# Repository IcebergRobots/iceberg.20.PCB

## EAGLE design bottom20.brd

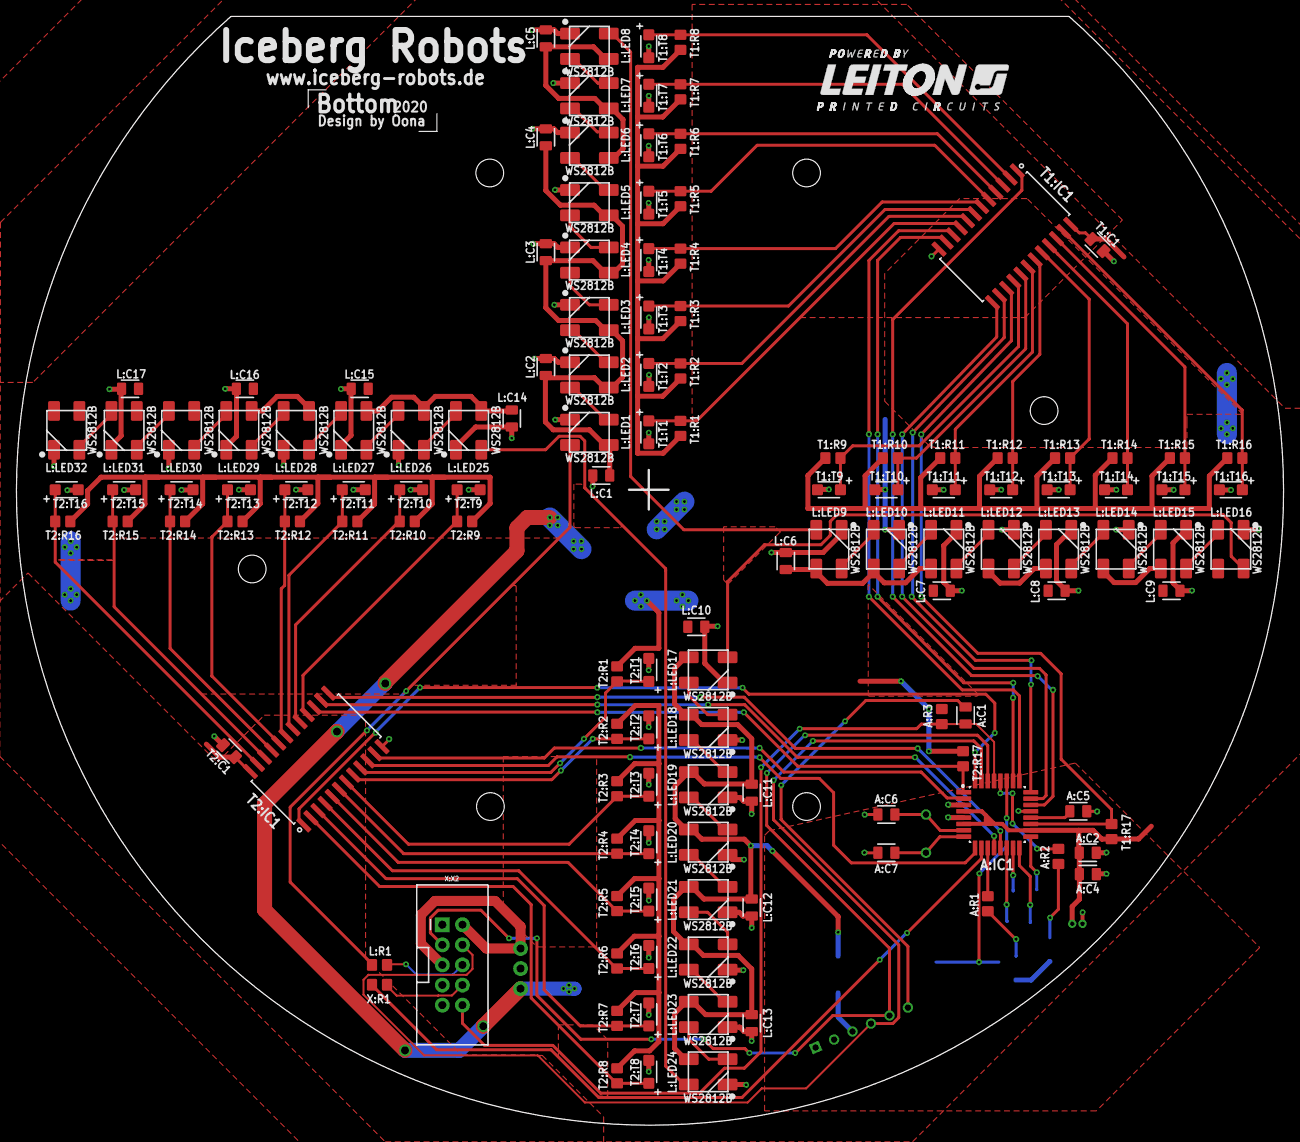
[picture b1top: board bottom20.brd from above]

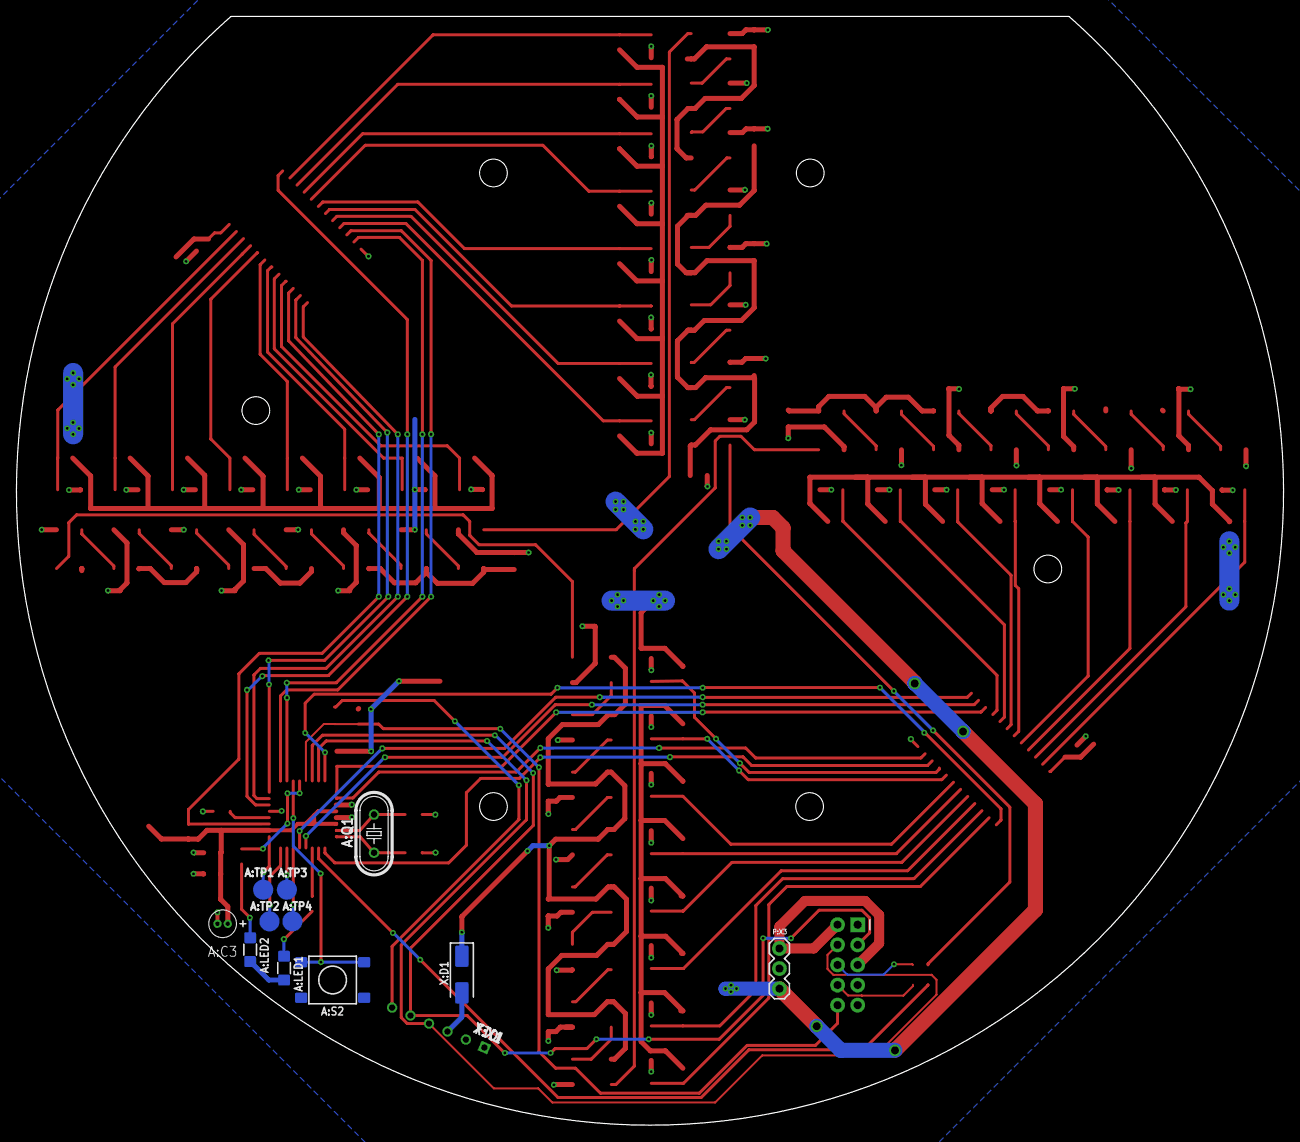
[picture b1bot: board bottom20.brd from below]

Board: 2 copper layers, 160.0 x 140.0 mm, 144 parts (12 on the bottom side), 99 nets.

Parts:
A:C1, A:C5: 100n; C0805
A:C2, A:C4: 1u; C0805
A:C3: 4,7 µF, 16 V, ±20%, 3x5 mm; CAPACITOR-THT-3
A:C6, A:C7: 15p; C0805
A:IC1: ATMEGA328P-AU
A:LED1, A:LED2: LED-GREEN1; 1206
A:Q1: 16MHz; CRYSTAL_HC49U-V
A:R1, A:R2: 110R; R0805
A:R3: 100k; R0805
A:S2: SMD-BUTTON; SWITCH-6MM-SMD
A:TP1: SCK; TESTPAD_B2,54
A:TP2: MISO; TESTPAD_B2,54
A:TP3: MOSI; TESTPAD_B2,54
A:TP4: SS; TESTPAD_B2,54
L:C1: 1u; C0805
L:C2, L:C3, L:C4, L:C5, L:C6, L:C7, L:C8, L:C9, L:C10, L:C11, L:C12, L:C13, L:C14, L:C15, L:C16, L:C17: 100n; C0805
L:LED1, L:LED2, L:LED3, L:LED4, L:LED5, L:LED6, L:LED7, L:LED8, L:LED9, L:LED10, L:LED11, L:LED12, L:LED13, L:LED14, L:LED15, L:LED16, L:LED17, L:LED18, L:LED19, L:LED20, L:LED21, L:LED22, L:LED23, L:LED24, L:LED25, L:LED26, L:LED27, L:LED28, L:LED29, L:LED30, L:LED31, L:LED32: WS2812B; 5050
L:R1: 330R; R0805
P:X3: SCHALTREGLER; 3X1
T1:C1, T2:C1: 100nF; C0805
T1:IC1, T2:IC1: MULTIPLEXER; SO24
T1:R1, T1:R2, T1:R3, T1:R4, T1:R5, T1:R6, T1:R7, T1:R8, T1:R9, T1:R10, T1:R11, T1:R12, T1:R13, T1:R14, T1:R15, T1:R16, T2:R1, T2:R2, T2:R3, T2:R4, T2:R5, T2:R6, T2:R7, T2:R8, T2:R9, T2:R10, T2:R11, T2:R12, T2:R13, T2:R14, T2:R15, T2:R16: 20k; R0805
T1:R17, T2:R17: 10k; R0805
T1:T1, T1:T2, T1:T3, T1:T4, T1:T5, T1:T6, T1:T7, T1:T8, T1:T9, T1:T10, T1:T11, T1:T12, T1:T13, T1:T14, T1:T15, T1:T16, T2:T1, T2:T2, T2:T3, T2:T4, T2:T5, T2:T6, T2:T7, T2:T8, T2:T9, T2:T10, T2:T11, T2:T12, T2:T13, T2:T14, T2:T15, T2:T16: SFH320; PLCC-2
X:D1: DIODE; DO-214BA
X:R1: 330R; R0805
X:X1: FTDI; PIN-HEADER-ANGLED-6
X:X2: WANNENSTECKER-10; 2X5-SHROUDED

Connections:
+5V: A:C2.1, A:C3.1, A:C4.1, A:IC1.4, A:IC1.6, A:IC1.18, A:R3.2, L:C1.1, L:C2.1, L:C3.1, L:C4.1, L:C5.1, L:C6.1, L:C7.1, L:C8.1, L:C9.1, L:C10.1, L:C11.1, L:C12.1, L:C13.1, L:C14.1, L:C15.1, L:C16.1, L:C17.1, L:LED1.VDD, L:LED2.VDD, L:LED3.VDD, L:LED4.VDD, L:LED5.VDD, L:LED6.VDD, L:LED7.VDD, L:LED8.VDD, L:LED9.VDD, L:LED10.VDD, L:LED11.VDD, L:LED12.VDD, L:LED13.VDD, L:LED14.VDD, L:LED15.VDD, L:LED16.VDD, L:LED17.VDD, L:LED18.VDD, L:LED19.VDD, L:LED20.VDD, L:LED21.VDD, L:LED22.VDD, L:LED23.VDD, L:LED24.VDD, L:LED25.VDD, L:LED26.VDD, L:LED27.VDD, L:LED28.VDD, L:LED29.VDD, L:LED30.VDD, L:LED31.VDD, L:LED32.VDD, P:X3.1, T1:C1.1, T1:IC1.24, T1:R1.2, T1:R2.2, T1:R3.2, T1:R4.2, T1:R5.2, T1:R6.2, T1:R7.2, T1:R8.2, T1:R9.2, T1:R10.2, T1:R11.2, T1:R12.2, T1:R13.2, T1:R14.2, T1:R15.2, T1:R16.2, T1:R17.1, T2:C1.1, T2:IC1.24, T2:R1.2, T2:R2.2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
+12V: P:X3.3, X:X2.2, X:X2.5
A:MISO: A:IC1.16, A:TP2.TP
A:MOSI: A:IC1.15, A:TP3.TP
A:N$1: A:IC1.11, A:R1.1
A:N$2: A:C7.1, A:IC1.8, A:Q1.1
A:N$3: A:C6.2, A:IC1.7, A:Q1.2
A:N$4: A:LED1.A, A:R1.2
A:N$8: A:C5.1, A:IC1.20
A:N$9: A:IC1.27, A:S2.A1, A:S2.A2
A:N$10: A:LED2.A, A:R2.2
A:N$11: A:IC1.28, A:R2.1
A:SCK: A:IC1.17, A:TP1.TP
A:SS: A:IC1.14, A:TP4.TP
ARD-INTERRUPT: A:IC1.10, X:R1.2
ARD-RESET: A:C1.2, A:IC1.29, A:R3.1, X:X2.10
DTR: A:C1.1, X:X1.6
GND: A:C2.2, A:C3.2, A:C4.2, A:C5.2, A:C6.1, A:C7.2, A:IC1.3, A:IC1.5, A:IC1.21, A:LED1.C, A:LED2.C, A:S2.B1, A:S2.B2, L:C1.2, L:C2.2, L:C3.2, L:C4.2, L:C5.2, L:C6.2, L:C7.2, L:C8.2, L:C9.2, L:C10.2, L:C11.2, L:C12.2, L:C13.2, L:C14.2, L:C15.2, L:C16.2, L:C17.2, L:LED1.GND, L:LED2.GND, L:LED3.GND, L:LED4.GND, L:LED5.GND, L:LED6.GND, L:LED7.GND, L:LED8.GND, L:LED9.GND, L:LED10.GND, L:LED11.GND, L:LED12.GND, L:LED13.GND, L:LED14.GND, L:LED15.GND, L:LED16.GND, L:LED17.GND, L:LED18.GND, L:LED19.GND, L:LED20.GND, L:LED21.GND, L:LED22.GND, L:LED23.GND, L:LED24.GND, L:LED25.GND, L:LED26.GND, L:LED27.GND, L:LED28.GND, L:LED29.GND, L:LED30.GND, L:LED31.GND, L:LED32.GND, P:X3.2, T1:C1.2, T1:IC1.12, T1:T1.C, T1:T2.C, T1:T3.C, T1:T4.C, T1:T5.C, T1:T6.C, T1:T7.C, T1:T8.C, T1:T9.C, T1:T10.C, T1:T11.C, T1:T12.C, T1:T13.C, T1:T14.C, T1:T15.C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
L:CON-1: L:LED8.OUT, L:LED9.IN
L:CON-2: L:LED16.OUT, L:LED17.IN
L:CON-3: L:LED24.OUT, L:LED25.IN
L:LED-IN1: L:LED2.OUT, L:LED3.IN
L:LED-IN2: L:LED4.OUT, L:LED5.IN
L:LED-IN3: L:LED6.OUT, L:LED7.IN
L:LED-IN4: L:LED26.OUT, L:LED27.IN
L:LED-IN5: L:LED10.OUT, L:LED11.IN
L:LED-IN6: L:LED12.OUT, L:LED13.IN
L:LED-IN7: L:LED14.OUT, L:LED15.IN
L:LED-IN8: L:LED28.OUT, L:LED29.IN
L:LED-IN9: L:LED18.OUT, L:LED19.IN
L:LED-IN10: L:LED20.OUT, L:LED21.IN
L:LED-IN11: L:LED22.OUT, L:LED23.IN
L:LED-IN12: L:LED30.OUT, L:LED31.IN
L:N$1: L:LED3.OUT, L:LED4.IN
L:N$2: L:LED1.OUT, L:LED2.IN
L:N$3: L:LED25.OUT, L:LED26.IN
L:N$4: L:LED5.OUT, L:LED6.IN
L:N$5: L:LED27.OUT, L:LED28.IN
L:N$6: L:LED29.OUT, L:LED30.IN
L:N$7: L:LED7.OUT, L:LED8.IN
L:N$8: L:LED31.OUT, L:LED32.IN
L:N$9: L:LED9.OUT, L:LED10.IN
L:N$10: L:LED1.IN, L:R1.1
L:N$11: L:LED11.OUT, L:LED12.IN
L:N$12: L:LED13.OUT, L:LED14.IN
L:N$13: L:LED15.OUT, L:LED16.IN
L:N$14: L:LED17.OUT, L:LED18.IN
L:N$16: L:LED19.OUT, L:LED20.IN
L:N$17: L:LED21.OUT, L:LED22.IN
L:N$18: L:LED23.OUT, L:LED24.IN
LED-IN: L:R1.2, X:X2.6
unnamed: A:IC1.32, T2:IC1.1
unnamed: A:IC1.1, T2:IC1.15, T2:R17.2
unnamed: A:IC1.2, T2:IC1.11
unnamed: A:IC1.9, T2:IC1.10
unnamed: A:IC1.12, T2:IC1.14
unnamed: A:IC1.13, T2:IC1.13
unnamed: A:IC1.23, T1:IC1.13
unnamed: A:IC1.24, T1:IC1.14
unnamed: A:IC1.25, T1:IC1.10
unnamed: A:IC1.26, T1:IC1.11
unnamed: A:IC1.19, T1:IC1.15, T1:R17.2
unnamed: A:IC1.22, T1:IC1.1
RX: A:IC1.30, X:X1.5, X:X2.3
T1:N$1: T1:IC1.9, T1:R1.1, T1:T1.A
T1:N$2: T1:IC1.8, T1:R2.1, T1:T2.A
T1:N$3: T1:IC1.7, T1:R3.1, T1:T3.A
T1:N$4: T1:IC1.6, T1:R4.1, T1:T4.A
T1:N$5: T1:IC1.5, T1:R5.1, T1:T5.A
T1:N$7: T1:IC1.16, T1:R9.1, T1:T9.A
T1:N$9: T1:IC1.2, T1:R8.1, T1:T8.A
T1:N$10: T1:IC1.3, T1:R7.1, T1:T7.A
T1:N$11: T1:IC1.4, T1:R6.1, T1:T6.A
T1:N$12: T1:IC1.17, T1:R10.1, T1:T10.A
T1:N$14: T1:IC1.18, T1:R11.1, T1:T11.A
T1:N$18: T1:IC1.20, T1:R13.1, T1:T13.A
T1:N$20: T1:IC1.21, T1:R14.1, T1:T14.A
T1:N$22: T1:IC1.22, T1:R15.1, T1:T15.A
T1:N$25: T1:IC1.23, T1:R16.1, T1:T16.A
T1:N$26: T1:IC1.19, T1:R12.1, T1:T12.A
T2:N$1: T2:IC1.9, T2:R1.1, T2:T1.A
T2:N$2: T2:IC1.8, T2:R2.1, T2:T2.A
T2:N$3: T2:IC1.7, T2:R3.1, T2:T3.A
T2:N$4: T2:IC1.6, T2:R4.1, T2:T4.A
T2:N$5: T2:IC1.5, T2:R5.1, T2:T5.A
T2:N$7: T2:IC1.16, T2:R9.1, T2:T9.A
T2:N$9: T2:IC1.2, T2:R8.1, T2:T8.A
T2:N$10: T2:IC1.3, T2:R7.1, T2:T7.A
T2:N$11: T2:IC1.4, T2:R6.1, T2:T6.A
T2:N$12: T2:IC1.17, T2:R10.1, T2:T10.A
T2:N$14: T2:IC1.18, T2:R11.1, T2:T11.A
T2:N$18: T2:IC1.20, T2:R13.1, T2:T13.A
T2:N$20: T2:IC1.21, T2:R14.1, T2:T14.A
T2:N$22: T2:IC1.22, T2:R15.1, T2:T15.A
T2:N$25: T2:IC1.23, T2:R16.1, T2:T16.A
T2:N$26: T2:IC1.19, T2:R12.1, T2:T12.A
TX: A:IC1.31, X:X1.4, X:X2.4
X:N$1: X:R1.1, X:X2.8
X:VID: X:D1.2, X:X1.3

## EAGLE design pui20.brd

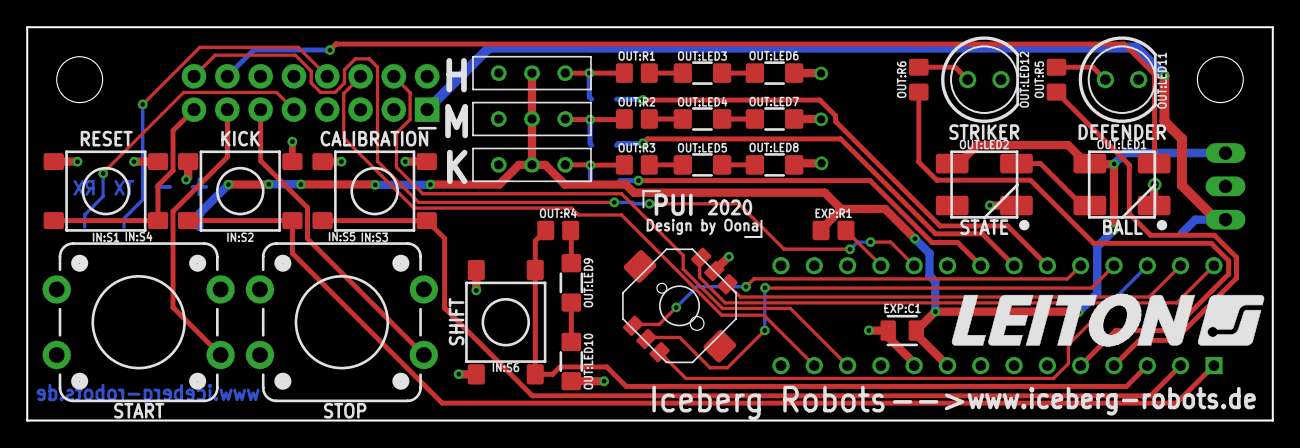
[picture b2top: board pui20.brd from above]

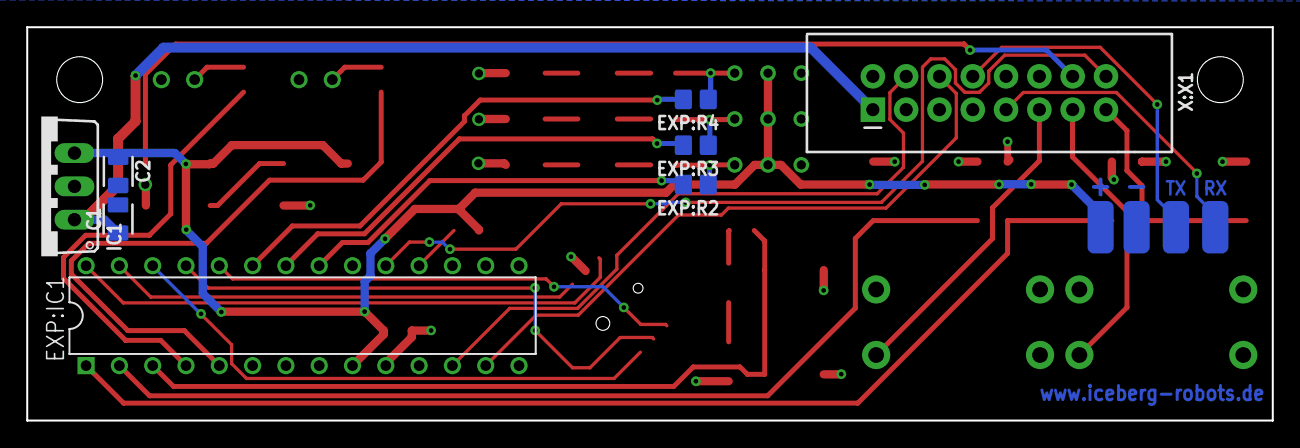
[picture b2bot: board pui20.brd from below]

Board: 2 copper layers, 95.0 x 30.0 mm, 42 parts (12 on the bottom side), 40 nets.

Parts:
C1, C2: 200nF; C0805
DISPLAY1:GND, DISPLAY1:RX, DISPLAY1:TX, DISPLAY1:VIN: TESTPAD-LONG
EXP:C1: 200nF; C0805
EXP:IC1: GPIO-EXPANDER; DIL28-3
EXP:R1: 1k; R0805
EXP:R2, EXP:R3, EXP:R4: 330R; R0805
IC1: L7805; TO220V
IN:S1, IN:S2, IN:S3, IN:S6: SMD-BUTTON; SWITCH-6MM-SMD
IN:S4, IN:S5: BUTTON-12MM; SWITCH-12MM-THT
IN:S7, IN:S8, IN:S9: TOGGLE-SWITCH
IN:U$1: JOYSTICK; SKRHAAE010
OUT:LED1, OUT:LED2: WS2812B; 5050
OUT:LED3, OUT:LED4, OUT:LED5, OUT:LED6, OUT:LED7, OUT:LED8, OUT:LED9, OUT:LED10: LED-GREEN1; 1206
OUT:LED11, OUT:LED12: LED-GREEN-THT; LED_LED5MM
OUT:R1, OUT:R2, OUT:R3, OUT:R4: 50R; R0805
OUT:R5, OUT:R6: 220R; R0805
X:X1: WANNENSTECKER-16; 2X8

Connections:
+5V: C2.1, DISPLAY1:VIN.P$1, EXP:C1.1, EXP:IC1.9, EXP:R1.2, IC1.3, IN:S7.C, IN:S8.C, IN:S9.C, OUT:LED1.VDD, OUT:LED2.VDD
+12V: C1.1, IC1.1, X:X1.1
CALIBRATION-B: EXP:IC1.2, IN:S3.A1, IN:S3.A2
CENTER-J: EXP:IC1.25, IN:U$1.CENTER
DEFENCE-LED: EXP:IC1.5, OUT:R6.1
DOWN-J: EXP:IC1.26, IN:U$1.C
EXP:N$1: EXP:IC1.21, EXP:R2.2
EXP:N$2: EXP:IC1.22, EXP:R3.2
EXP:N$3: EXP:IC1.23, EXP:R4.2
EXP:RESET: EXP:IC1.18, EXP:R1.1
GND: C1.2, C2.2, DISPLAY1:GND.P$1, EXP:C1.2, EXP:IC1.10, EXP:IC1.15, EXP:IC1.16, EXP:IC1.17, IC1.2, IN:S1.B1, IN:S1.B2, IN:S2.B1, IN:S2.B2, IN:S3.B1, IN:S3.B2, IN:S4.3, IN:S5.3, IN:S6.B1, IN:S6.B2, IN:U$1.COMMON, OUT:LED1.GND, OUT:LED2.GND, OUT:LED6.C, OUT:LED7.C, OUT:LED8.C, OUT:LED10.C, OUT:LED11.K, OUT:LED12.K, X:X1.3, X:X1.5, X:X1.7
HEADSTART-LED: EXP:R4.1, IN:S7.A, OUT:R1.1
INT-B: EXP:IC1.19, X:X1.16
KICK-B: EXP:IC1.1, IN:S2.A1, IN:S2.A2
KICKER-LED: EXP:R2.1, IN:S9.A, OUT:R3.1
LED-IN: OUT:LED1.IN, X:X1.14
LEFT-J: EXP:IC1.24, IN:U$1.A
MOTOR-LED: EXP:R3.1, IN:S8.A, OUT:R2.1
OUT:N$1: OUT:LED3.C, OUT:LED6.A
OUT:N$2: OUT:LED3.A, OUT:R1.2
OUT:N$3: OUT:LED4.C, OUT:LED7.A
OUT:N$4: OUT:LED5.C, OUT:LED8.A
OUT:N$5: OUT:LED1.OUT, OUT:LED2.IN
OUT:N$6: OUT:LED4.A, OUT:R2.2
OUT:N$7: OUT:LED5.A, OUT:R3.2
OUT:N$8: OUT:LED11.A, OUT:R5.2
OUT:N$9: OUT:LED12.A, OUT:R6.2
OUT:N$11: OUT:LED9.A, OUT:R4.2
OUT:N$12: OUT:LED9.C, OUT:LED10.A
RESET-B: IN:S1.A1, IN:S1.A2, X:X1.15
RIGHT-J: EXP:IC1.27, IN:U$1.D
RX: DISPLAY1:RX.P$1, X:X1.9
SCL: EXP:IC1.12, X:X1.4
SDA: EXP:IC1.13, X:X1.6
SHIFT-LED: EXP:IC1.3, IN:S6.A1, IN:S6.A2, OUT:R4.1
START-B: IN:S4.1, X:X1.13
STOP-B: IN:S5.1, X:X1.11
STRIKER-LED: EXP:IC1.4, OUT:R5.1
TX: DISPLAY1:TX.P$1, X:X1.8
UP-J: EXP:IC1.28, IN:U$1.B

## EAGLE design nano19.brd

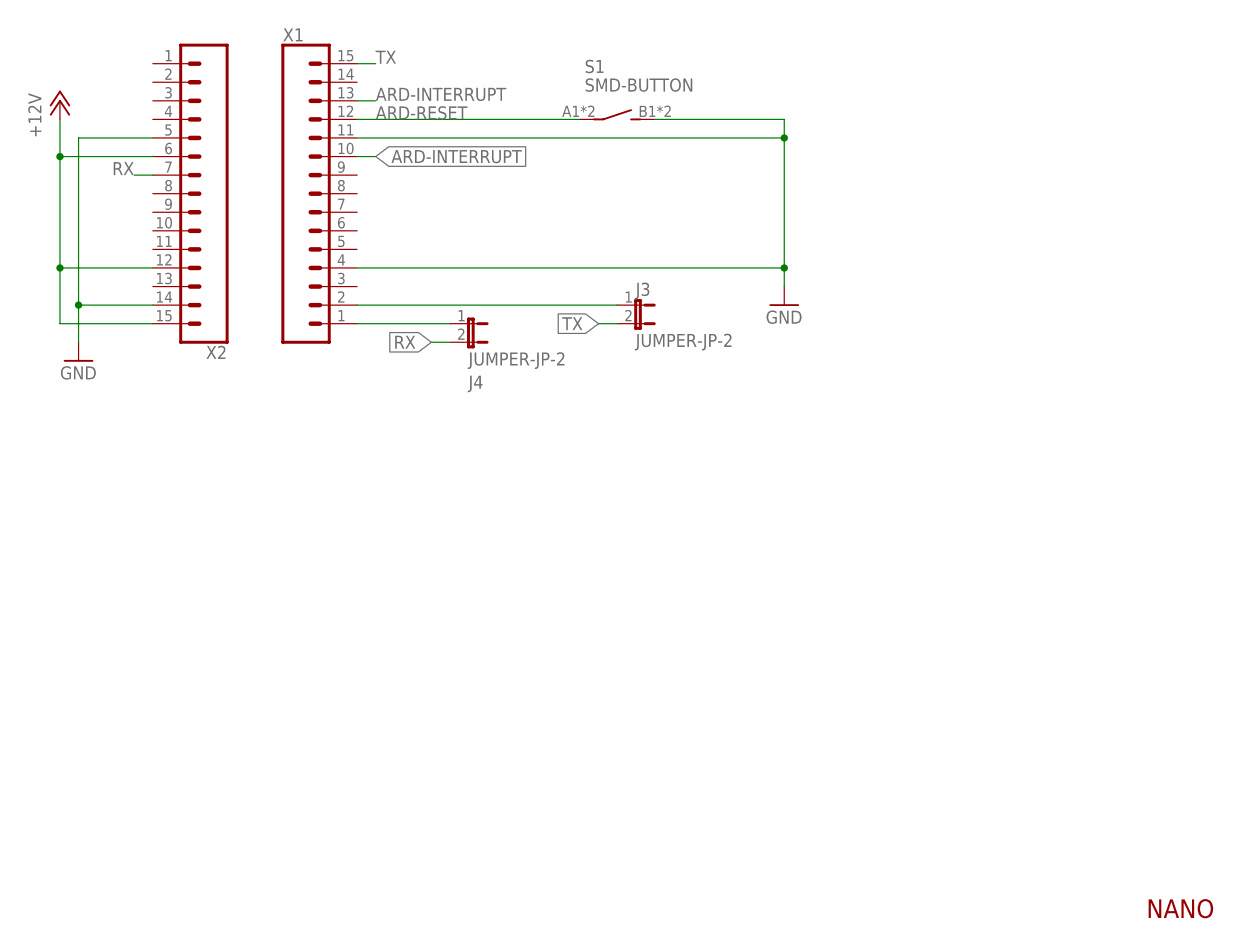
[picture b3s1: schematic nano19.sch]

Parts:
J3, J4: JUMPER-JP-2; JUMPER_JP1
S1: SMD-BUTTON; SWITCH-6MM-SMD
X1, X2: CONN_15; 1X15

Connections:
+12V: X2.6, X2.12, X2.15
ARD-INTERRUPT: X1.10, X1.13
ARD-RESET: S1.A1, S1.A2, X1.12
GND: S1.B1 (S), S1.B2 (S), X1.4, X1.11, X2.5, X2.14
unnamed: J3.1, X1.2
unnamed: J4.1, X1.1
RX: J4.2, X2.7
TX: J3.2, X1.15

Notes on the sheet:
NANO

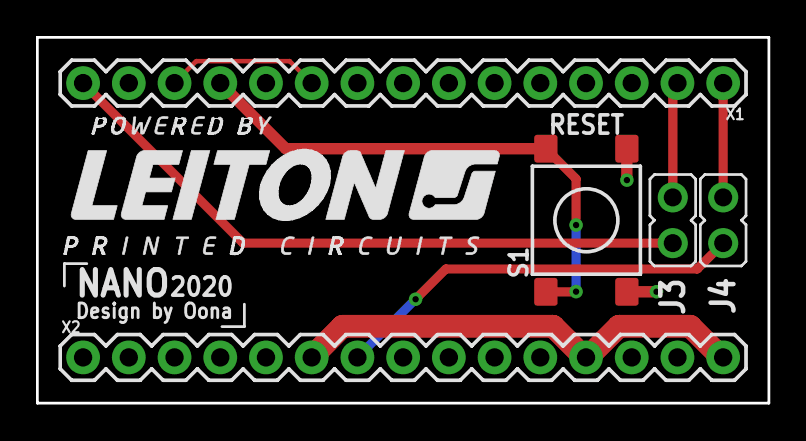
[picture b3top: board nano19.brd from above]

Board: 2 copper layers, 40.6 x 20.3 mm, 5 parts (0 on the bottom side), 8 nets.

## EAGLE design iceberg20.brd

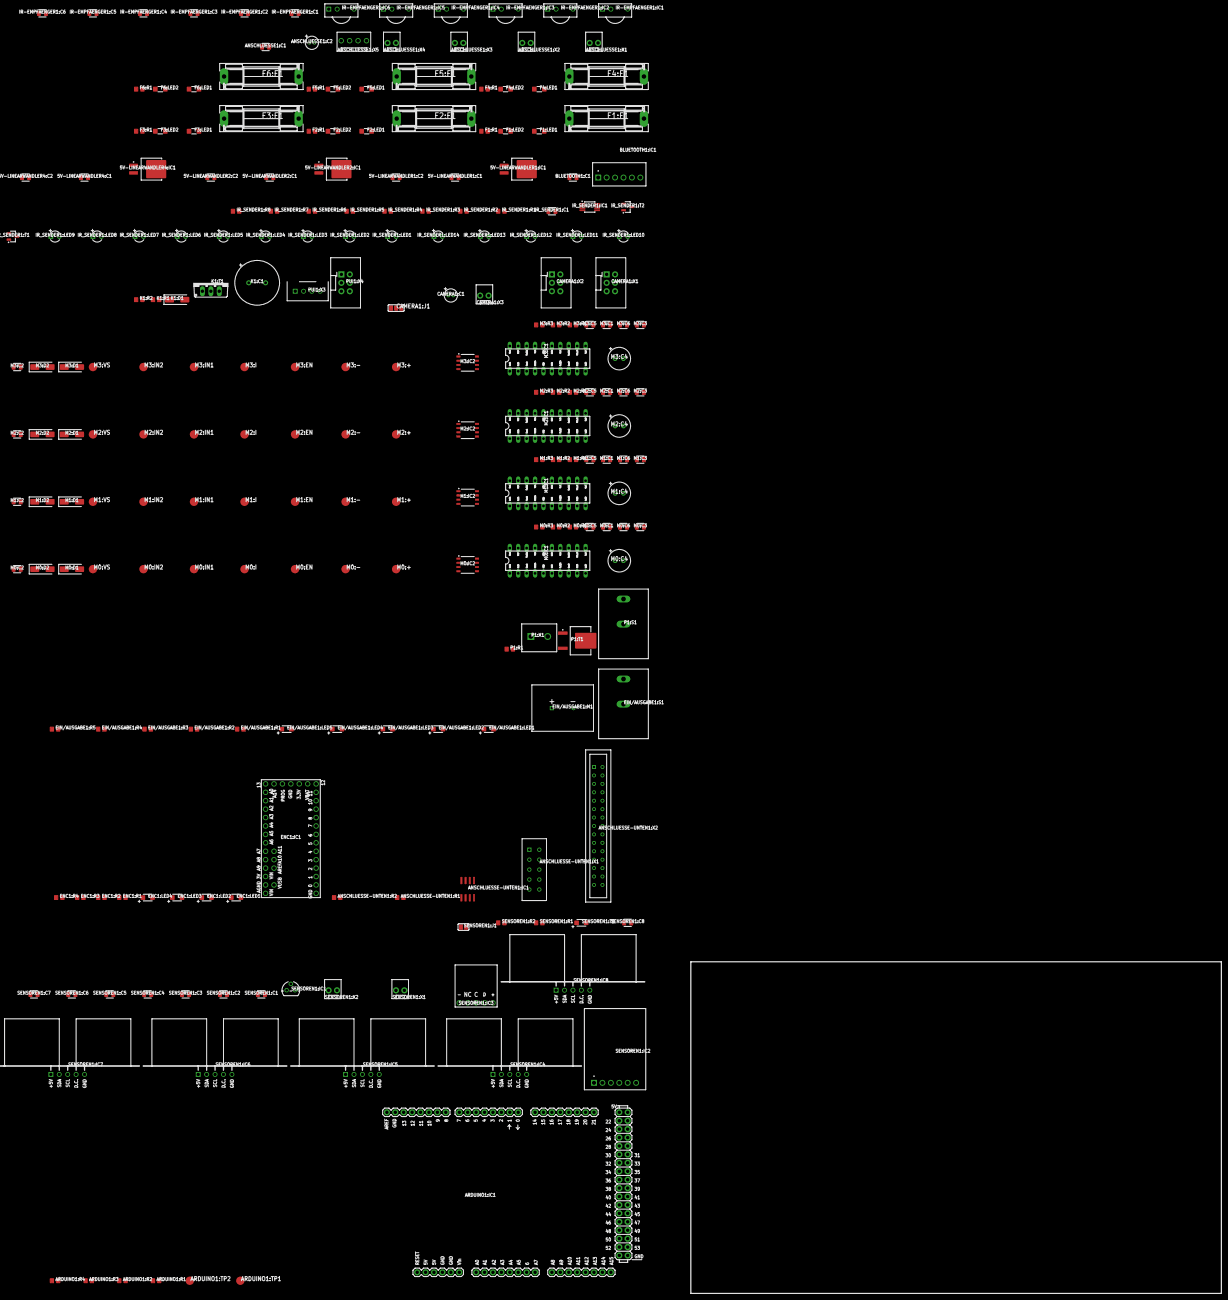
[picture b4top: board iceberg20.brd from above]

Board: 2 copper layers, 160.0 x 100.0 mm, 231 parts (0 on the bottom side), 169 nets, no tracks yet.

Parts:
5V-LINEARWANDLER1:C1, 5V-LINEARWANDLER2:C1, 5V-LINEARWANDLER4:C1: 100n; C0805
5V-LINEARWANDLER1:C2, 5V-LINEARWANDLER2:C2, 5V-LINEARWANDLER4:C2: 330n; C0805
5V-LINEARWANDLER1:IC1, 5V-LINEARWANDLER2:IC1, 5V-LINEARWANDLER4:IC1: L7805CV; DPAK
ANSCHLUESSE1:C1: 100n; C0805
ANSCHLUESSE1:C2: 1 uF, 50 V, ±20 %; CAPACITOR-THT-4
ANSCHLUESSE1:X1, ANSCHLUESSE1:X2, ANSCHLUESSE1:X3, ANSCHLUESSE1:X4: PS25/2GPS25/2GWS-1X02; CON-01X02
ANSCHLUESSE1:X5: PS25/4G; CON-01X04
ANSCHLUESSE-UNTEN1:IC1: P82B96; SO8
ANSCHLUESSE-UNTEN1:R1, ANSCHLUESSE-UNTEN1:R2: 10k; R0805
ANSCHLUESSE-UNTEN1:X1: BUCHSENLEISTE-10; 2X5
ANSCHLUESSE-UNTEN1:X2: WANNENSTECKER-30; 2X15
ARDUINO1:IC1: ARUINO-MEGA; ARDUINO_MEGA
ARDUINO1:R1, ARDUINO1:R2: 1k; R0805
ARDUINO1:R3, ARDUINO1:R4: 100k; R0805
ARDUINO1:TP1, ARDUINO1:TP2: TESTPAD; TESTPAD_B2,54
BLUETOOTH1:C1: 100n; C0805
BLUETOOTH1:IC1: HC-05
CAMERA1:C1: 1 uF, 50 V, ±20 %; CAPACITOR-THT-4
CAMERA1:J1: JUMPER; JUMPER-SJ-3
CAMERA1:X1, CAMERA1:X2: WANNENSTECKER-6; 2X3
CAMERA1:X3: PS25/2GPS25/2GWS-1X02; CON-01X02
EIN/AUSGABE1:LED1, EIN/AUSGABE1:LED2: GREEN; PLCC-2
EIN/AUSGABE1:LED3, EIN/AUSGABE1:LED4, EIN/AUSGABE1:LED5: LED-WHITE; PLCC-2
EIN/AUSGABE1:M1: SPEAKER
EIN/AUSGABE1:R1, EIN/AUSGABE1:R2: 100R; R0805
EIN/AUSGABE1:R3, EIN/AUSGABE1:R4, EIN/AUSGABE1:R5: 120R; R0805
EIN/AUSGABE1:S1: SWITCH; 1801.2106
ENC1:IC1: TEENSY-3.2; TEENSY-3
ENC1:LED1, ENC1:LED2, ENC1:LED3, ENC1:LED4: LED-WHITE; PLCC-2
ENC1:R1, ENC1:R2, ENC1:R3, ENC1:R4: 120R; R0805
F1:F1, F2:F1, F3:F1, F4:F1, F5:F1, F6:F1: SH22,5
F1:LED1, F1:LED2, F2:LED1, F2:LED2, F3:LED1, F3:LED2, F4:LED1, F4:LED2, F5:LED1, F5:LED2, F6:LED1, F6:LED2: LED-GREEN1; 1206
F1:R1, F2:R1, F3:R1, F4:R1, F5:R1, F6:R1: 270R; R0805
IR-EMPFAENGER1:C1, IR-EMPFAENGER1:C2, IR-EMPFAENGER1:C3, IR-EMPFAENGER1:C4, IR-EMPFAENGER1:C5, IR-EMPFAENGER1:C6: 100n; C0805
IR-EMPFAENGER1:IC1, IR-EMPFAENGER1:IC2, IR-EMPFAENGER1:IC3, IR-EMPFAENGER1:IC4, IR-EMPFAENGER1:IC5, IR-EMPFAENGER1:IC6: TSOP31433; TSOP312
IR_SENDER1:C1: 100n; C0805
IR_SENDER1:IC1: DS1099; USOP-8
IR_SENDER1:LED1, IR_SENDER1:LED2, IR_SENDER1:LED3, IR_SENDER1:LED4, IR_SENDER1:LED5, IR_SENDER1:LED6, IR_SENDER1:LED7, IR_SENDER1:LED8, IR_SENDER1:LED9, IR_SENDER1:LED10, IR_SENDER1:LED11, IR_SENDER1:LED12, IR_SENDER1:LED13, IR_SENDER1:LED14: IR-LED; LED-3MM
IR_SENDER1:R1, IR_SENDER1:R2, IR_SENDER1:R4, IR_SENDER1:R6: 100k; R0805
IR_SENDER1:R3, IR_SENDER1:R5: 100R; R0805
IR_SENDER1:R7, IR_SENDER1:R8: 15R; R0805
IR_SENDER1:T1, IR_SENDER1:T2: KMA3D6N20SA; SOT23
K1:C1: 2,2 mF, 16 V, ±20 %; CAPACITOR-THT-13
K1:D1: DIODE; DO-214BA
K1:R1: 300R; R0805
K1:R2: 100k; R0805
K1:T1: IRF1405; TO220V
M0:+, M0:-, M0:EN, M0:I, M0:IN1, M0:IN2, M0:VS, M1:+, M1:-, M1:EN, M1:I, M1:IN1, M1:IN2, M1:VS, M2:+, M2:-, M2:EN, M2:I, M2:IN1, M2:IN2, M2:VS, M3:+, M3:-, M3:EN, M3:I, M3:IN1, M3:IN2, M3:VS: TESTPAD; TESTPAD_B2,54
M0:C1, M1:C1, M2:C1, M3:C1: 10nF; C0805
M0:C2, M1:C2, M2:C2, M3:C2: 220nF; C0805
M0:C3, M0:C6, M1:C3, M1:C6, M2:C3, M2:C6, M3:C3, M3:C6: 100nF; C0805
M0:C4, M1:C4, M2:C4, M3:C4: 100uF, 16V, ±20 %; CAPACITOR-THT-6.3
M0:C5, M1:C5, M2:C5, M3:C5: 1nF; C0805
M0:D1, M0:D2, M1:D1, M1:D2, M2:D1, M2:D2, M3:D1, M3:D2: DIODE; DO-214BA
M0:IC1, M1:IC1, M2:IC1, M3:IC1: L6205N; DIL20
M0:IC2, M1:IC2, M2:IC2, M3:IC2: ACS712ACS712-SOIC-8; SOIC-8
M0:R1, M1:R1, M2:R1, M3:R1: 100R; R0805
M0:R2, M1:R2, M2:R2, M3:R2: 100k; R0805
M0:R3, M1:R3, M2:R3, M3:R3: 10k; R0805
P1:R1: 100k; R0805
P1:S1: SWITCH; 1801.2106
P1:T1: AOD403; TO252
P1:X1: TERMINAL-2; LIB_WECO121
PUI1:X3: JST-XH-4; XH-4
PUI1:X4: WANNENSTECKER-6; 2X3
SENSOREN1:C1, SENSOREN1:C2, SENSOREN1:C3, SENSOREN1:C4, SENSOREN1:C5, SENSOREN1:C6, SENSOREN1:C7, SENSOREN1:C8: 100n; C0805
SENSOREN1:IC1: LM-35; TO-92
SENSOREN1:IC2: CMPS12
SENSOREN1:IC3: RTC
SENSOREN1:IC4, SENSOREN1:IC5, SENSOREN1:IC6, SENSOREN1:IC7, SENSOREN1:IC8: SRF-08
SENSOREN1:J1: JUMPER-2; SJ
SENSOREN1:R1: 20k; R0805
SENSOREN1:R2: 470; R0805
SENSOREN1:T1: SFH320; PLCC-2
SENSOREN1:X1, SENSOREN1:X2: PS25/2GPS25/2GWS-1X02; CON-01X02

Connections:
5V-CAMERA: 5V-LINEARWANDLER2:C1.1, 5V-LINEARWANDLER2:IC1.2, CAMERA1:J1.1, CAMERA1:X2.2, CAMERA1:X2.5
5V-PUI: 5V-LINEARWANDLER4:C1.1, 5V-LINEARWANDLER4:IC1.2, PUI1:X3.P$1
12V-PUI: 5V-LINEARWANDLER4:C2.1, 5V-LINEARWANDLER4:IC1.1, F3:F1.2, F3:R1.2, PUI1:X4.6
+5V: 5V-LINEARWANDLER1:C1.1, 5V-LINEARWANDLER1:IC1.2, ANSCHLUESSE1:C1.1, ANSCHLUESSE1:X1.1, ANSCHLUESSE1:X5.4, ANSCHLUESSE-UNTEN1:X2.1, ANSCHLUESSE-UNTEN1:X2.5, ANSCHLUESSE-UNTEN1:X2.9, ANSCHLUESSE-UNTEN1:X2.13, BLUETOOTH1:C1.1, BLUETOOTH1:IC1.5, EIN/AUSGABE1:R1.2, ENC1:IC1.VIN, IR-EMPFAENGER1:C1.1, IR-EMPFAENGER1:C2.1, IR-EMPFAENGER1:C3.1, IR-EMPFAENGER1:C4.1, IR-EMPFAENGER1:C5.1, IR-EMPFAENGER1:C6.1, IR-EMPFAENGER1:IC1.2, IR-EMPFAENGER1:IC2.2, IR-EMPFAENGER1:IC3.2, IR-EMPFAENGER1:IC4.2, IR-EMPFAENGER1:IC5.2, IR-EMPFAENGER1:IC6.2, IR_SENDER1:C1.1, IR_SENDER1:IC1.3, IR_SENDER1:R1.2, IR_SENDER1:R2.2, M0:C6.1, M0:IC2.8, M1:C6.1, M1:IC2.8, M2:C6.1, M2:IC2.8, M3:C6.1, M3:IC2.8, SENSOREN1:C1.1, SENSOREN1:C2.1, SENSOREN1:C3.1, SENSOREN1:C4.1, SENSOREN1:C5.1, SENSOREN1:C6.1, SENSOREN1:C7.1, SENSOREN1:C8.1, SENSOREN1:IC1.3, SENSOREN1:IC2.1, SENSOREN1:IC3.+, SENSOREN1:IC4.1, SENSOREN1:IC5.1, SENSOREN1:IC6.1, SENSOREN1:IC7.1, SENSOREN1:IC8.1, SENSOREN1:R1.2
+12V: F1:F1.1, F2:F1.1, F3:F1.1, F4:F1.1, F5:F1.1, F6:F1.1
A1: ANSCHLUESSE1:X3.1, ARDUINO1:IC1.A10
ANSCHLUESSE-UNTEN1:SCL-12V: ANSCHLUESSE-UNTEN1:IC1.5, ANSCHLUESSE-UNTEN1:IC1.6, ANSCHLUESSE-UNTEN1:R2.1, ANSCHLUESSE-UNTEN1:X2.26
ANSCHLUESSE-UNTEN1:SDA-12V: ANSCHLUESSE-UNTEN1:IC1.2, ANSCHLUESSE-UNTEN1:IC1.3, ANSCHLUESSE-UNTEN1:R1.1, ANSCHLUESSE-UNTEN1:X2.23
ANSCHLUSS-12V: ANSCHLUESSE-UNTEN1:IC1.8, ANSCHLUESSE-UNTEN1:R1.2, ANSCHLUESSE-UNTEN1:R2.2, ANSCHLUESSE-UNTEN1:X2.19, ANSCHLUESSE-UNTEN1:X2.27, ANSCHLUESSE-UNTEN1:X2.28, F4:F1.2, F4:R1.2
ARDUINO1:+5V: ARDUINO1:IC1.5V@0, ARDUINO1:IC1.5V@1, ARDUINO1:IC1.5V@2, ARDUINO1:R1.2, ARDUINO1:R2.2, ARDUINO1:R3.2, ARDUINO1:R4.2
ARDUINO1:N$1: ARDUINO1:IC1.A11, ARDUINO1:TP2.TP
ARDUINO1:N$2: ARDUINO1:IC1.24, ARDUINO1:TP1.TP
BR-I: ARDUINO1:IC1.A6, SENSOREN1:X1.2
BR-LED: ARDUINO1:IC1.A9, SENSOREN1:R2.2
CAMERA1:5V-CAMERA: CAMERA1:J1.2, CAMERA1:X1.2
CLK: ARDUINO1:IC1.52, CAMERA1:X1.3
CS: ARDUINO1:IC1.53, CAMERA1:X1.5
D1: ANSCHLUESSE1:X4.1, ARDUINO1:IC1.43
EIN/AUSGABE1:N$1: EIN/AUSGABE1:LED1.A, EIN/AUSGABE1:R1.1
EIN/AUSGABE1:N$2: EIN/AUSGABE1:LED2.A, EIN/AUSGABE1:R2.1
EIN/AUSGABE1:N$3: EIN/AUSGABE1:LED3.A, EIN/AUSGABE1:R3.1
EIN/AUSGABE1:N$4: EIN/AUSGABE1:LED4.A, EIN/AUSGABE1:R5.1
EIN/AUSGABE1:N$5: EIN/AUSGABE1:LED5.A, EIN/AUSGABE1:R4.1
EN-B: ARDUINO1:IC1.22, BLUETOOTH1:IC1.6
ENA0: ANSCHLUESSE-UNTEN1:X2.2, ENC1:IC1.2
ENA1: ANSCHLUESSE-UNTEN1:X2.6, ENC1:IC1.4
ENA2: ANSCHLUESSE-UNTEN1:X2.10, ENC1:IC1.14
ENA3: ANSCHLUESSE-UNTEN1:X2.14, ENC1:IC1.16
ENB0: ANSCHLUESSE-UNTEN1:X2.3, ENC1:IC1.3
ENB1: ANSCHLUESSE-UNTEN1:X2.7, ENC1:IC1.5
ENB2: ANSCHLUESSE-UNTEN1:X2.11, ENC1:IC1.15
ENB3: ANSCHLUESSE-UNTEN1:X2.15, ENC1:IC1.17
ENC1:LED1: ENC1:IC1.20, ENC1:R1.2
ENC1:LED2: ENC1:IC1.21, ENC1:R2.2
ENC1:LED3: ENC1:IC1.22, ENC1:R3.2
ENC1:LED4: ENC1:IC1.23, ENC1:R4.2
ENC1:N$3: ENC1:LED1.A, ENC1:R1.1
ENC1:N$4: ENC1:LED2.A, ENC1:R2.1
ENC1:N$5: ENC1:LED3.A, ENC1:R3.1
ENC1:N$8: ENC1:LED4.A, ENC1:R4.1
ETC-12V: 5V-LINEARWANDLER1:C2.1, 5V-LINEARWANDLER1:IC1.1, 5V-LINEARWANDLER2:C2.1, 5V-LINEARWANDLER2:IC1.1, ANSCHLUESSE1:C2.1, ANSCHLUESSE1:X2.1, CAMERA1:C1.1, CAMERA1:J1.3, CAMERA1:X3.2, F6:F1.2, F6:R1.2, IR_SENDER1:R7.2, IR_SENDER1:R8.2
F1:N$1: F1:LED1.A, F1:R1.1
F1:N$165: F1:LED1.C, F1:LED2.A
F2:N$1: F2:LED1.A, F2:R1.1
F2:N$165: F2:LED1.C, F2:LED2.A
F3:N$1: F3:LED1.A, F3:R1.1
F3:N$165: F3:LED1.C, F3:LED2.A
F4:N$1: F4:LED1.A, F4:R1.1
F4:N$165: F4:LED1.C, F4:LED2.A
F5:N$1: F5:LED1.A, F5:R1.1
F5:N$165: F5:LED1.C, F5:LED2.A
F6:N$1: F6:LED1.A, F6:R1.1
F6:N$165: F6:LED1.C, F6:LED2.A
GND: 5V-LINEARWANDLER1:C1.2, 5V-LINEARWANDLER1:C2.2, 5V-LINEARWANDLER1:IC1.3, 5V-LINEARWANDLER2:C1.2, 5V-LINEARWANDLER2:C2.2, 5V-LINEARWANDLER2:IC1.3, 5V-LINEARWANDLER4:C1.2, 5V-LINEARWANDLER4:C2.2, 5V-LINEARWANDLER4:IC1.3, ANSCHLUESSE1:C1.2, ANSCHLUESSE1:C2.2, ANSCHLUESSE1:X1.2, ANSCHLUESSE1:X2.2, ANSCHLUESSE1:X3.2, ANSCHLUESSE1:X4.2, ANSCHLUESSE1:X5.2, ANSCHLUESSE-UNTEN1:IC1.4, ANSCHLUESSE-UNTEN1:X2.4, ANSCHLUESSE-UNTEN1:X2.8, ANSCHLUESSE-UNTEN1:X2.12, ANSCHLUESSE-UNTEN1:X2.16, ANSCHLUESSE-UNTEN1:X2.17, ANSCHLUESSE-UNTEN1:X2.20, ANSCHLUESSE-UNTEN1:X2.22, ANSCHLUESSE-UNTEN1:X2.24, ANSCHLUESSE-UNTEN1:X2.25, ANSCHLUESSE-UNTEN1:X2.30, ARDUINO1:IC1.GND@0, ARDUINO1:IC1.GND@1, ARDUINO1:IC1.GND@2, ARDUINO1:IC1.GND@3, ARDUINO1:IC1.GND@4, BLUETOOTH1:C1.2, BLUETOOTH1:IC1.4, CAMERA1:C1.2, CAMERA1:X1.6, CAMERA1:X2.1, CAMERA1:X2.6, CAMERA1:X3.1, EIN/AUSGABE1:LED2.C, EIN/AUSGABE1:LED3.C, EIN/AUSGABE1:LED4.C, EIN/AUSGABE1:LED5.C, EIN/AUSGABE1:M1.2, EIN/AUSGABE1:S1.1, ENC1:IC1.AGND, ENC1:IC1.GND, ENC1:IC1.GND1, ENC1:LED1.C, ENC1:LED2.C, ENC1:LED3.C, ENC1:LED4.C, F1:LED2.C, F2:LED2.C, F3:LED2.C, F4:LED2.C, F5:LED2.C, F6:LED2.C, IR-EMPFAENGER1:C1.2, IR-EMPFAENGER1:C2.2, IR-EMPFAENGER1:C3.2, IR-EMPFAENGER1:C4.2, IR-EMPFAENGER1:C5.2, IR-EMPFAENGER1:C6.2, IR-EMPFAENGER1:IC1.1, IR-EMPFAENGER1:IC2.1, IR-EMPFAENGER1:IC3.1, IR-EMPFAENGER1:IC4.1, IR-EMPFAENGER1:IC5.1, IR-EMPFAENGER1:IC6.1, IR_SENDER1:C1.2, IR_SENDER1:IC1.4, IR_SENDER1:R4.1, IR_SENDER1:R6.1, IR_SENDER1:T1.1, IR_SENDER1:T2.1, K1:C1.2, K1:R2.1, K1:T1.3, M0:C3.2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
HEARTBEAT: ARDUINO1:IC1.3, EIN/AUSGABE1:LED1.C, EIN/AUSGABE1:R2.2
I-M0: ARDUINO1:IC1.36, M0:I.TP, M0:IC2.7
I-M1: ARDUINO1:IC1.37, M1:I.TP, M1:IC2.7
I-M2: M2:I.TP, M2:IC2.7
I-M3: ARDUINO1:IC1.38, ARDUINO1:IC1.39, M3:I.TP, M3:IC2.7
INTERRUPT: ANSCHLUESSE-UNTEN1:X2.18, ARDUINO1:IC1.2, ARDUINO1:R4.1
IR-EN1: ARDUINO1:IC1.41, IR_SENDER1:IC1.5, IR_SENDER1:R1.1
IR-EN2: ARDUINO1:IC1.42, IR_SENDER1:IC1.6, IR_SENDER1:R2.1
IR-SIG1: ARDUINO1:IC1.A0, IR-EMPFAENGER1:IC1.3
IR-SIG2: ARDUINO1:IC1.A1, IR-EMPFAENGER1:IC2.3
IR-SIG3: ARDUINO1:IC1.A2, IR-EMPFAENGER1:IC3.3
IR-SIG4: ARDUINO1:IC1.A3, IR-EMPFAENGER1:IC4.3
IR-SIG5: ARDUINO1:IC1.A4, IR-EMPFAENGER1:IC5.3
IR-SIG6: ARDUINO1:IC1.A5, IR-EMPFAENGER1:IC6.3
IR_SENDER1:N$1: IR_SENDER1:R3.2, IR_SENDER1:R4.2, IR_SENDER1:T1.2
IR_SENDER1:N$2: IR_SENDER1:IC1.1, IR_SENDER1:R5.1
IR_SENDER1:N$3: IR_SENDER1:LED1.2, IR_SENDER1:T1.3
IR_SENDER1:N$4: IR_SENDER1:LED1.1, IR_SENDER1:LED2.2
IR_SENDER1:N$5: IR_SENDER1:LED2.1, IR_SENDER1:LED3.2
IR_SENDER1:N$6: IR_SENDER1:LED3.1, IR_SENDER1:LED4.2
IR_SENDER1:N$7: IR_SENDER1:LED4.1, IR_SENDER1:LED5.2
IR_SENDER1:N$8: IR_SENDER1:LED5.1, IR_SENDER1:LED6.2
IR_SENDER1:N$9: IR_SENDER1:LED6.1, IR_SENDER1:LED7.2
IR_SENDER1:N$10: IR_SENDER1:R5.2, IR_SENDER1:R6.2, IR_SENDER1:T2.2
IR_SENDER1:N$11: IR_SENDER1:IC1.2, IR_SENDER1:R3.1
IR_SENDER1:N$12: IR_SENDER1:LED8.2, IR_SENDER1:T2.3
IR_SENDER1:N$13: IR_SENDER1:LED8.1, IR_SENDER1:LED9.2
IR_SENDER1:N$14: IR_SENDER1:LED9.1, IR_SENDER1:LED10.2
IR_SENDER1:N$15: IR_SENDER1:LED10.1, IR_SENDER1:LED11.2
IR_SENDER1:N$16: IR_SENDER1:LED11.1, IR_SENDER1:LED12.2
IR_SENDER1:N$17: IR_SENDER1:LED12.1, IR_SENDER1:LED13.2
IR_SENDER1:N$18: IR_SENDER1:LED13.1, IR_SENDER1:LED14.2
IR_SENDER1:N$19: IR_SENDER1:LED14.1, IR_SENDER1:R8.1
IR_SENDER1:N$20: IR_SENDER1:LED7.1, IR_SENDER1:R7.1
K1:N$1: K1:R1.2, K1:R2.2, K1:T1.1
KICK: F5:F1.2, F5:R1.2
KICK+: ANSCHLUESSE-UNTEN1:X1.9, K1:C1.1, K1:D1.1
KICK-: ANSCHLUESSE-UNTEN1:X1.10, K1:D1.2, K1:T1.2
KICK-EN: ARDUINO1:IC1.8, K1:R1.1
LED1: ARDUINO1:IC1.5, EIN/AUSGABE1:R3.2
LED2: ARDUINO1:IC1.6, EIN/AUSGABE1:R5.2
LED3: ARDUINO1:IC1.7, EIN/AUSGABE1:R4.2
M0:FILTER: M0:C5.1, M0:IC2.6
M0:M-: M0:IC1.13, M0:IC1.18, M0:IC2.3, M0:IC2.4
M0:N$4: M0:D1.2, M0:D2.1, M0:R1.2
M0:N$6: M0:C2.2, M0:D1.1, M0:IC1.12
M0:N$7: M0:C1.1, M0:R1.1
M0:N$8: M0:C1.2, M0:IC1.19
M0:N$9: M0:EN.TP, M0:IC1.11, M0:IC1.20, M0:R2.2
M1:FILTER: M1:C5.1, M1:IC2.6
M1:M-: M1:IC1.13, M1:IC1.18, M1:IC2.3, M1:IC2.4
M1:N$4: M1:D1.2, M1:D2.1, M1:R1.2
M1:N$6: M1:C2.2, M1:D1.1, M1:IC1.12
M1:N$7: M1:C1.1, M1:R1.1
M1:N$8: M1:C1.2, M1:IC1.19
M1:N$9: M1:EN.TP, M1:IC1.11, M1:IC1.20, M1:R2.2
M2:FILTER: M2:C5.1, M2:IC2.6
M2:M-: M2:IC1.13, M2:IC1.18, M2:IC2.3, M2:IC2.4
M2:N$4: M2:D1.2, M2:D2.1, M2:R1.2
M2:N$6: M2:C2.2, M2:D1.1, M2:IC1.12
M2:N$7: M2:C1.1, M2:R1.1
M2:N$8: M2:C1.2, M2:IC1.19
M2:N$9: M2:EN.TP, M2:IC1.11, M2:IC1.20, M2:R2.2
M3:FILTER: M3:C5.1, M3:IC2.6
M3:M-: M3:IC1.13, M3:IC1.18, M3:IC2.3, M3:IC2.4
M3:N$4: M3:D1.2, M3:D2.1, M3:R1.2
M3:N$6: M3:C2.2, M3:D1.1, M3:IC1.12
M3:N$7: M3:C1.1, M3:R1.1
M3:N$8: M3:C1.2, M3:IC1.19
M3:N$9: M3:EN.TP, M3:IC1.11, M3:IC1.20, M3:R2.2
M-DIR-A0: ARDUINO1:IC1.28, M0:IC1.1, M0:IC1.9, M0:IN1.TP
M-DIR-A1: ARDUINO1:IC1.30, M1:IC1.1, M1:IC1.9, M1:IN1.TP
M-DIR-A2: ARDUINO1:IC1.32, M2:IC1.1, M2:IC1.9, M2:IN1.TP
M-DIR-A3: ARDUINO1:IC1.34, M3:IC1.1, M3:IC1.9, M3:IN1.TP
M-DIR-B0: ARDUINO1:IC1.29, M0:IC1.2, M0:IC1.10, M0:IN2.TP
M-DIR-B1: ARDUINO1:IC1.31, M1:IC1.2, M1:IC1.10, M1:IN2.TP
M-DIR-B2: ARDUINO1:IC1.33, M2:IC1.2, M2:IC1.10, M2:IN2.TP
M-DIR-B3: ARDUINO1:IC1.35, M3:IC1.2, M3:IC1.10, M3:IN2.TP
M-EN0: ARDUINO1:IC1.10, M0:R2.1, M0:R3.2
M-EN1: ARDUINO1:IC1.11, M1:R2.1, M1:R3.2
M-EN2: ARDUINO1:IC1.12, M2:R2.1, M2:R3.2
M-EN3: ARDUINO1:IC1.13, M3:R2.1, M3:R3.2
MA0: ANSCHLUESSE-UNTEN1:X1.1, M0:-.TP, M0:IC2.1, M0:IC2.2
MA1: ANSCHLUESSE-UNTEN1:X1.3, M1:-.TP, M1:IC2.1, M1:IC2.2
MA2: ANSCHLUESSE-UNTEN1:X1.5, M2:-.TP, M2:IC2.1, M2:IC2.2
MA3: ANSCHLUESSE-UNTEN1:X1.7, ANSCHLUESSE-UNTEN1:X1.8, M3:-.TP, M3:IC2.1, M3:IC2.2
MB0: ANSCHLUESSE-UNTEN1:X1.2, M0:+.TP, M0:IC1.4, M0:IC1.7
MB1: ANSCHLUESSE-UNTEN1:X1.4, M1:+.TP, M1:IC1.4, M1:IC1.7
MB2: ANSCHLUESSE-UNTEN1:X1.6, M2:+.TP, M2:IC1.4, M2:IC1.7
MB3: M3:+.TP, M3:IC1.4, M3:IC1.7
MISO: ARDUINO1:IC1.50, CAMERA1:X1.1
MOSI: ARDUINO1:IC1.51, CAMERA1:X1.4
MOTOR-12V: F1:F1.2, F1:R1.2, M0:C2.1, M0:C3.1, M0:C4.1, M0:D2.2, M0:IC1.14, M0:IC1.17, M0:VS.TP, M1:C2.1, M1:C3.1, M1:C4.1, M1:D2.2, M1:IC1.14, M1:IC1.17, M1:VS.TP, M2:C2.1, M2:C3.1, M2:C4.1, M2:D2.2, M2:IC1.14, M2:IC1.17, M2:VS.TP, M3:C2.1, M3:C3.1, M3:C4.1, M3:D2.2, M3:IC1.14, M3:IC1.17, M3:VS.TP
unnamed: ARDUINO1:IC1.VIN, F2:F1.2, F2:R1.2
P1:N$1: P1:S1.1, P1:X1.P2
P1:N$2: P1:S1.2, P1:T1.3
P1:N$4: P1:R1.2, P1:T1.1
PHOTO: ARDUINO1:IC1.A7, SENSOREN1:R1.1, SENSOREN1:T1.A
RESET: ARDUINO1:IC1.RESET, ARDUINO1:R3.1, PUI1:X4.4
RGBLED: ANSCHLUESSE-UNTEN1:X2.21, ARDUINO1:IC1.9
RST-NANO: ANSCHLUESSE-UNTEN1:X2.29, ARDUINO1:IC1.40
RX-B: ARDUINO1:IC1.17, BLUETOOTH1:IC1.3
RX-C: ARDUINO1:IC1.15, CAMERA1:X2.3
RX-P: ARDUINO1:IC1.19, PUI1:X3.P$3
SCL: ANSCHLUESSE1:X5.1, ANSCHLUESSE-UNTEN1:IC1.7, ARDUINO1:IC1.21, ARDUINO1:R2.1, ENC1:IC1.19, PUI1:X4.5, SENSOREN1:IC2.3, SENSOREN1:IC3.C, SENSOREN1:IC4.3, SENSOREN1:IC5.3, SENSOREN1:IC6.3, SENSOREN1:IC7.3, SENSOREN1:IC8.3
SDA: ANSCHLUESSE1:X5.3, ANSCHLUESSE-UNTEN1:IC1.1, ARDUINO1:IC1.20, ARDUINO1:R1.1, ENC1:IC1.18, PUI1:X4.2, SENSOREN1:IC2.2, SENSOREN1:IC3.D, SENSOREN1:IC4.2, SENSOREN1:IC5.2, SENSOREN1:IC6.2, SENSOREN1:IC7.2, SENSOREN1:IC8.2
SENSOREN1:N$1: SENSOREN1:IC2.4, SENSOREN1:J1.2
SENSOREN1:N$2: SENSOREN1:R2.1, SENSOREN1:X2.2
SPEAKER: ARDUINO1:IC1.4, EIN/AUSGABE1:M1.1
STATE-B: ARDUINO1:IC1.23, BLUETOOTH1:IC1.1
SWITCH: ARDUINO1:IC1.49, EIN/AUSGABE1:S1.2
TEMP: ARDUINO1:IC1.A8, SENSOREN1:IC1.2
TX-B: ARDUINO1:IC1.16, BLUETOOTH1:IC1.2
TX-C: ARDUINO1:IC1.14, CAMERA1:X2.4
TX-P: ARDUINO1:IC1.18, PUI1:X3.P$2

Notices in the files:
parts and their libraries:
SparkFun-Connectors: Licensing: Creative Commons ShareAlike 4.0 International - https://creativecommons.org/licenses/by-sa/4.0
